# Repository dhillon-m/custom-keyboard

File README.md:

# BHOO Keyboard

A custom wireless keyboard setup with two parts. This repo has the [ZMK](https://zmk.dev) firmware, the KiCad PCB and the case CAD.

| Device      | Role             | Description                                                     |
| ----------- | ---------------- | --------------------------------------------------------------- |
| **BHOO-75** | Split central    | Custom PCB, 75% ISO (UK) with an F-row and arrow cluster. 84 keys. |
| **BHOO-20** | Split peripheral | Handwired numpad with a 128×64 SSD1306 OLED (WIP). 19 keys.      |

Both run on a **nice!nano v2** (nRF52840). The BHOO-75 pairs with the host over Bluetooth or USB. The BHOO-20 connects to the BHOO-75 as a ZMK split peripheral, so both boards share **one keymap** and appear to the computer as a single keyboard.

## Features

- **Two boards, one keymap.** Positions 0–18 are the numpad and 19–102 are the main keyboard, all defined in [`bhoo_75.keymap`](config/boards/shields/bhoo_75/bhoo_75.keymap).
- **UK layout** via [`zmk-locales`](https://github.com/joelspadin/zmk-locales) (`keys_en_gb.h`).
- **OLED battery screen (WIP)** on the BHOO-20. See [below](#oled-display-work-in-progress).
- **Bluetooth layer** for switching between 4 profiles, clearing a pairing, and entering the bootloader.
- **Custom PCB and case.** The KiCad project and STEP/STL files are in [`hardware/`](hardware). See [Hardware](#hardware).
- **CI builds** on every push through GitHub Actions. A `settings_reset` image is built too.

## OLED display (work in progress)

> **Not working yet.** Nothing shows on the screen at the moment. The code and images below are the design being worked towards, not the current behaviour.

The planned screen shows two battery bars, one per device. Each bar will fill 1 px per percent, with a hand-drawn 5×9 percentage readout next to it. At 100% the number turns into a lightning bolt. The drawing is done directly on an LVGL canvas in [`battery_screen.c`](config/boards/shields/bhoo_20/battery_screen.c).

- **Top bar:** BHOO-75.
- **Bottom bar:** BHOO-20, meant to update from `zmk_battery_state_changed`.
- The panel is mounted upside down. The overlay is set up to rotate it in hardware with `segment-remap` and `com-invdir`.
- The display should blank when the keyboard is idle (`CONFIG_ZMK_DISPLAY_BLANK_ON_IDLE`).
- Even once the screen works, the BHOO-75 bar needs more wiring: `bhoo_battery_set_central()` exists, but nothing sends the central's battery level to the peripheral yet.

## Keymap

### Layer 0: Default

**BHOO-75**

```
Esc   F1  F2  F3  F4  F5  F6  F7  F8  F9  F10 F11 F12 Del  PrtSc
`     1   2   3   4   5   6   7   8   9   0   -   =   Bksp Home
Tab   Q   W   E   R   T   Y   U   I   O   P   [   ]        End
Caps  A   S   D   F   G   H   J   K   L   ;   '   #   Ent  PgUp
Shift \   Z   X   C   V   B   N   M   ,   .   /   Shift ↑  PgDn
Ctrl  Win Alt         Space           Alt Fn  Ctrl  ←   ↓   →
```

**BHOO-20**

```
            ┌─────┬─────┐
            │  —  │  —  │
┌─────┬─────┼─────┼─────┤
│ Num │  /  │  *  │  -  │
├─────┼─────┼─────┼─────┤
│  7  │  8  │  9  │     │
├─────┼─────┼─────┤  +  │
│  4  │  5  │  6  │     │
├─────┼─────┼─────┼─────┤
│  1  │  2  │  3  │     │
├─────┴─────┼─────┤ Ent │
│     0     │  .  │     │
└───────────┴─────┴─────┘
```

The two `—` keys at the top are unassigned (`&none`).

### Layer 1: Bluetooth (hold `Fn`)

| Key    | Action                           |
| ------ | -------------------------------- |
| F1–F4  | Select Bluetooth profile 0–3     |
| F5     | Clear the current profile's bond |
| F6     | Enter bootloader (BHOO-75)       |

## Repository layout

```
.
├── build.yaml                       # Build matrix (board + shield combos)
├── .github/workflows/build.yml      # Uses ZMK's reusable build workflow (v0.2)
├── config/
│   ├── west.yml                     # Pins ZMK v0.2 + zmk-locales
│   └── boards/shields/
│       ├── bhoo_75/                 # Main keyboard: central
│       │   ├── bhoo_75.overlay      # 6×15 GPIO matrix + transform (padded to 19 cols)
│       │   ├── bhoo_75.keymap       # Keymap for both devices
│       │   └── bhoo_75.conf         # Split central
│       └── bhoo_20/                 # Numpad: peripheral
│           ├── bhoo_20.overlay      # 6×4 GPIO matrix, SSD1306 on i2c0
│           ├── bhoo_20.conf         # Display, battery, LVGL canvas
│           ├── battery_screen.c     # Custom status screen (WIP)
│           └── CMakeLists.txt
├── hardware/
│   ├── bhoo_75/pcb/                 # KiCad 8 PCB project
│   ├── bhoo_75/case/                # Top case, bottom case, plate, foot (STEP)
│   └── bhoo_20/case/                # Numpad case parts (STL)
├── docs/images/                     # Photos, renders, OLED mock-ups
└── zephyr/module.yml
```

## Building

### GitHub Actions (recommended)

1. Push to any branch, or run the workflow manually from the **Actions** tab.
2. Open the finished run and download the **firmware** artifact.
3. It contains three images:
   - `bhoo_75-nice_nano_v2-zmk.uf2`
   - `bhoo_20-nice_nano_v2-zmk.uf2`
   - `settings_reset-nice_nano_v2-zmk.uf2`

### Local build

With a [ZMK development environment](https://zmk.dev/docs/development/local-toolchain/setup) set up:

```sh
west build -s zmk/app -d build/bhoo_75 -b nice_nano_v2 -- \
  -DSHIELD=bhoo_75 -DZMK_CONFIG="$(pwd)/config"

west build -s zmk/app -d build/bhoo_20 -b nice_nano_v2 -- \
  -DSHIELD=bhoo_20 -DZMK_CONFIG="$(pwd)/config"
```

## Flashing

1. Plug the nice!nano into USB and double-tap reset. It mounts as a USB drive (`NICENANO`).
2. Copy the matching `.uf2` onto the drive. It reboots on its own when the copy finishes.
3. Do the same for the other board.

**Pairing problems?** Flash `settings_reset` to **both** boards, then reflash the normal firmware. This clears stale split and Bluetooth bonds. Afterwards, remove the keyboard from your computer's Bluetooth list and pair it again.

## Hardware

### BHOO-75: custom PCB

The BHOO-75 uses a two-layer PCB designed in KiCad 8. It's about 336 mm wide, with:

- solder-in MX switch footprints
- one SOD-123 diode per key
- a nice!nano v2 and a LiPo battery on the underside

| Layout in KiCad | Bare board |
| --- | --- |
|  |  |
| **Populated (underside)** | **Diodes up close** |
|  |  |

| File | Description |
| --- | --- |
| [`hardware/bhoo_75/pcb/`](hardware/bhoo_75/pcb) | KiCad 8 project: schematic (`PCB.kicad_sch`) and board (`PCB.kicad_pcb`) |
| [`hardware/bhoo_75/case/Top Case.step`](hardware/bhoo_75/case) | Top case |
| [`hardware/bhoo_75/case/Bottom Case.step`](hardware/bhoo_75/case) | Bottom case |
| [`hardware/bhoo_75/case/Plate.step`](hardware/bhoo_75/case) | Switch plate |
| [`hardware/bhoo_75/case/Foot.step`](hardware/bhoo_75/case) | Foot |

**Opening the PCB in KiCad:** footprints are stored inside the board file, so the PCB opens without any extra libraries. To edit the schematic symbols or see the 3D view, you also need:

- [ScottoKicad](https://github.com/joe-scotto/scottokeebs): symbols, the nice!nano and diode footprints, and 3D models. Set the `SCOTTOKEEBS_KICAD` path variable to wherever you put it.
- [ai03 MX_V2](https://github.com/ai03-2725/MX_V2): the `MX_Solderable` switch footprints.

The switch 3D models point to a file on the original author's PC, so they won't show in the 3D viewer.

### BHOO-20: handwired numpad

The BHOO-20 is handwired: switches are wired directly into a 6 × 4 matrix with diodes, no PCB. Printable case parts are in [`hardware/bhoo_20/case/`](hardware/bhoo_20/case):

- `Top Case.stl`
- `Bottom Case.stl`
- `Plate.stl`
- `Foot.stl`

### Wiring

| Board   | Matrix | Diodes  | Rows (GPIO)                         | Columns (GPIO)                                                                    |
| ------- | ------ | ------- | ----------------------------------- | --------------------------------------------------------------------------------- |
| BHOO-75 | 6 × 15 | col2row | P1.02 P1.07 P1.06 P1.04 P0.11 P1.00 | P1.01 P0.02 P0.24 P0.22 P0.20 P0.17 P0.08 P0.06 P0.09 P0.10 P1.11 P1.13 P1.15 P0.29 P0.31 |
| BHOO-20 | 6 × 4  | col2row | P0.09 P0.10 P1.11 P1.13 P1.15 P0.02 | P0.24 P1.00 P0.11 P1.04                                                           |

The BHOO-20 OLED is an SSD1306 at I²C address `0x3C` on `i2c0`, using the nice!nano default SDA/SCL pins.

The BHOO-75 matrix transform declares 19 columns. Columns 15–18 are virtual padding that reserve key positions 0–18 for the BHOO-20, so a single keymap can cover both devices.

## Roadmap

- [ ] Get the BHOO-20 OLED working
- [ ] Send the BHOO-75 battery level to the BHOO-20 display
- [ ] More layers (media, navigation)

## Acknowledgements

- [ZMK Firmware](https://zmk.dev)
- [zmk-locales](https://github.com/joelspadin/zmk-locales) by Joel Spadin
- [nice!nano](https://nicekeyboards.com/nice-nano/)
- [ScottoKicad](https://github.com/joe-scotto/scottokeebs) by Joe Scotto
- [MX_V2](https://github.com/ai03-2725/MX_V2) by ai03

## License

Everything in this repository, including the firmware, the PCB and the case CAD, is released under the [MIT License](LICENSE).

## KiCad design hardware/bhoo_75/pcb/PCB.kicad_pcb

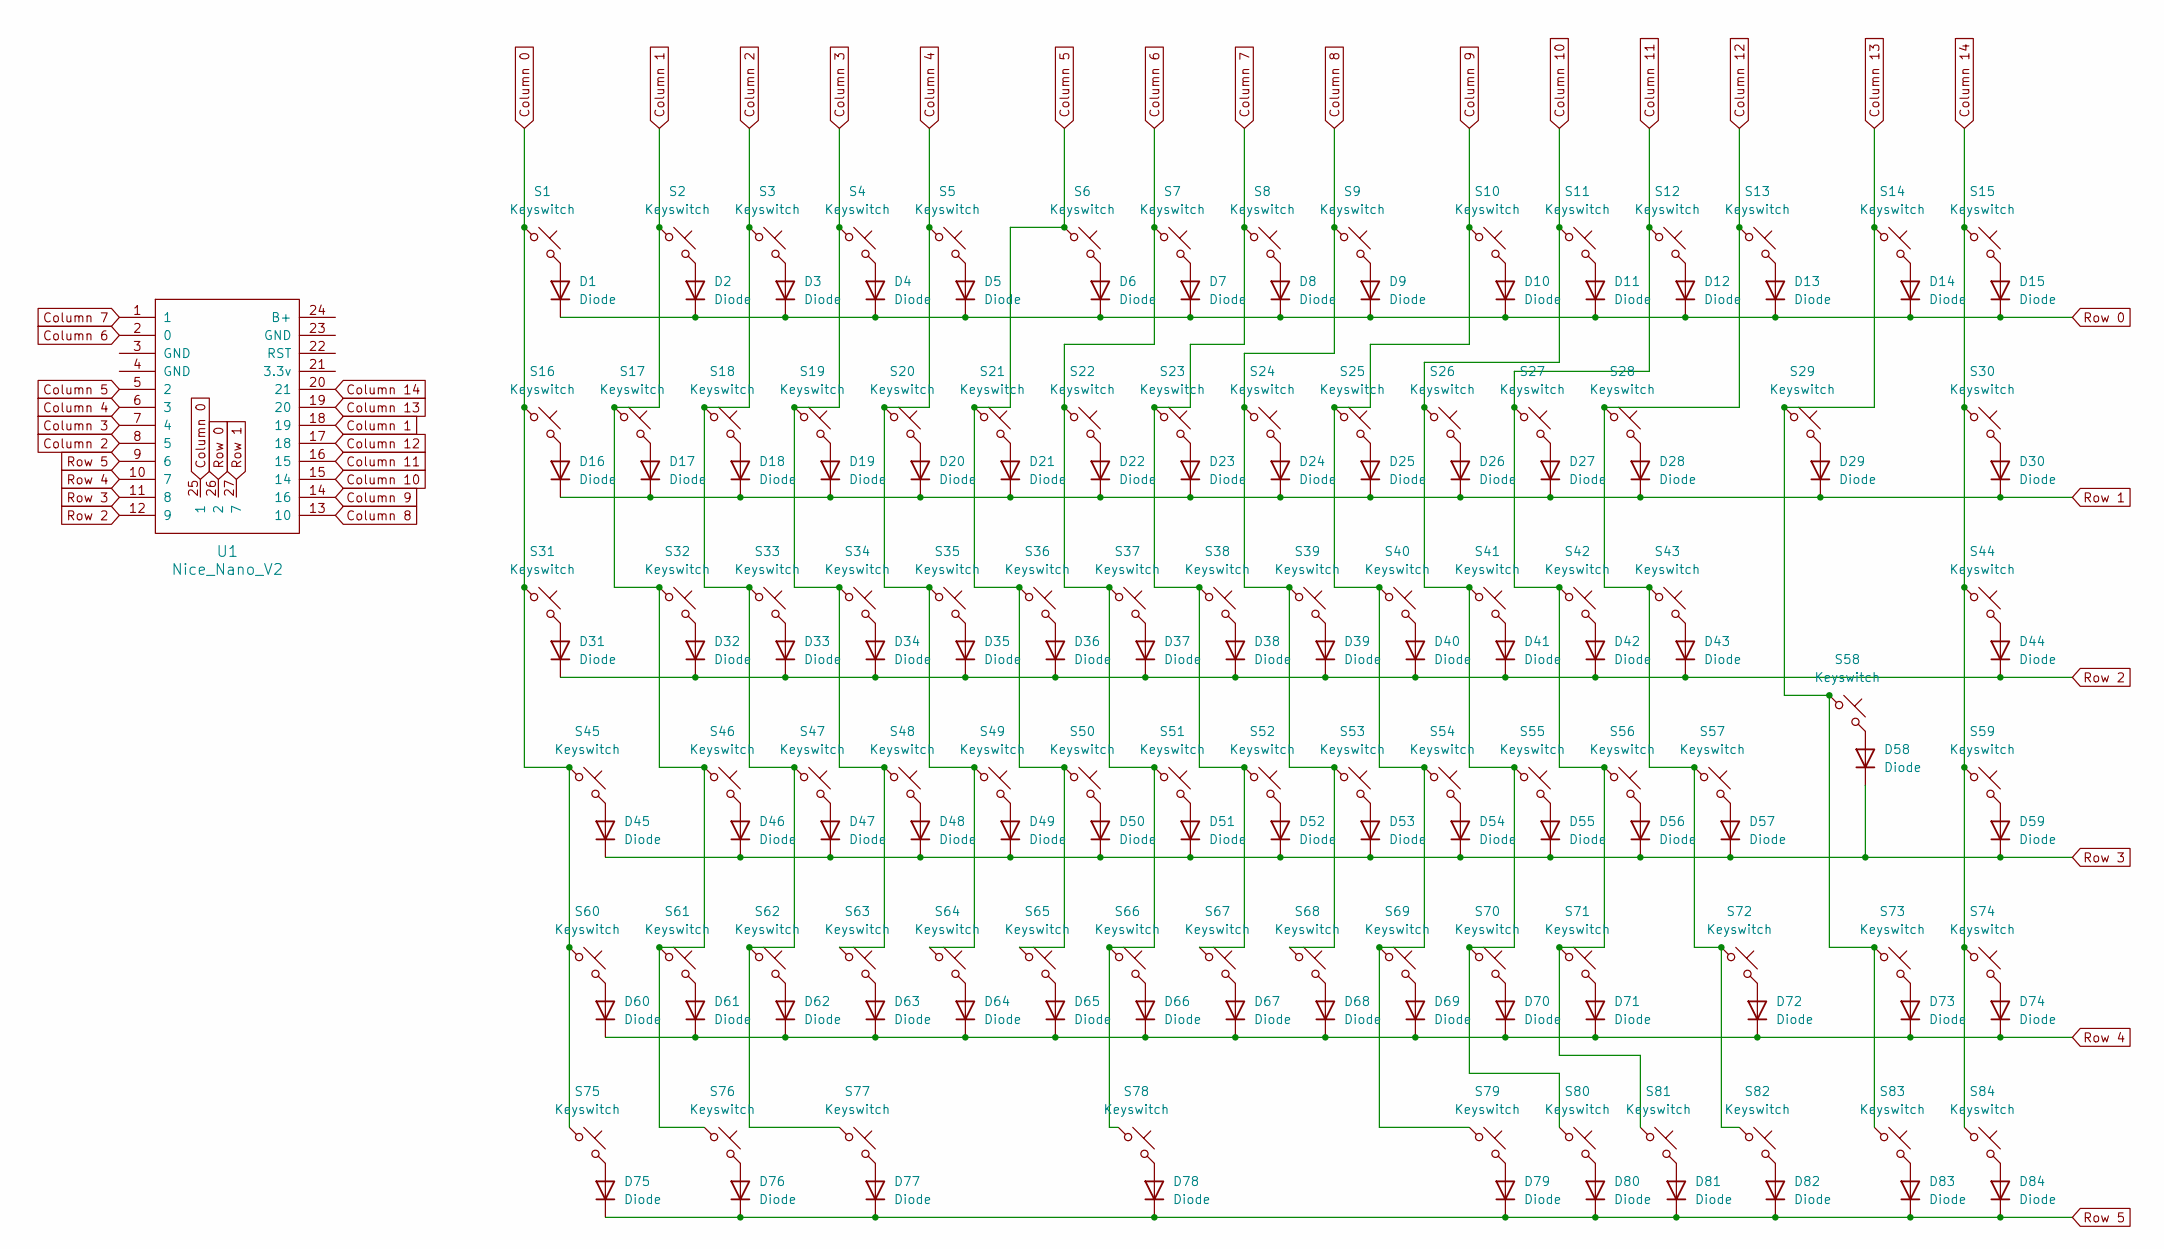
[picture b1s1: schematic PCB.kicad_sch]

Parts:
D1, D2, D3, D4, D5, D6, D7, D8, D9, D10, D11, D12, D13, D14, D15, D16, D17, D18, D19, D20, D21, D22, D23, D24, D25, D26, D27, D28, D29, D30, D31, D32, D33, D34, D35, D36, D37, D38, D39, D40, D41, D42, D43, D44, D45, D46, D47, D48, D49, D50, D51, D52, D53, D54, D55, D56, D57, D58, D59, D60, D61, D62, D63, D64, D65, D66, D67, D68, D69, D70, D71, D72, D73, D74, D75, D76, D77, D78, D79, D80, D81, D82, D83, D84: Diode; Diode_SOD-123
S1, S2, S3, S4, S5, S6, S7, S8, S9, S10, S11, S12, S13, S14, S15, S16, S17, S18, S19, S20, S21, S22, S23, S24, S25, S26, S27, S28, S30, S32, S33, S34, S35, S36, S37, S38, S39, S40, S41, S42, S43, S44, S46, S47, S48, S49, S50, S51, S52, S53, S54, S55, S56, S57, S59, S61, S62, S63, S64, S65, S66, S67, S68, S69, S70, S71, S73, S74, S79, S80, S81, S82, S83, S84: Keyswitch; MX-Solderable-1U
S29: Keyswitch; MX-Solderable-2U
S31: Keyswitch; MX-Solderable-1.5U
S45, S72: Keyswitch; MX-Solderable-1.75U
S58: Keyswitch; MX-Solderable-ISO
S60, S75, S76, S77: Keyswitch; MX-Solderable-1.25U
S78: Keyswitch; MX-Solderable-6.25U
U1: Nice_Nano_V2

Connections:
Column 0: S1.1, S16.1, S31.1, S45.1, S60.1, S75.1, U1.25 (1)
Column 1: S2.1, S17.1, S32.1, S46.1, S61.1, S76.1, U1.18 (19)
Column 2: S3.1, S18.1, S33.1, S47.1, S62.1, S77.1, U1.8 (5)
Column 3: S4.1, S19.1, S34.1, S48.1, S63.1, U1.7 (4)
Column 4: S5.1, S20.1, S35.1, S49.1, S64.1, U1.6 (3)
Column 5: S6.1, S21.1, S36.1, S50.1, S65.1, U1.5 (2)
Column 6: S7.1, S22.1, S37.1, S51.1, S66.1, S78.1, U1.2 (0)
Column 7: S8.1, S23.1, S38.1, S52.1, S67.1, U1.1
Column 8: S9.1, S24.1, S39.1, S53.1, S68.1, U1.13 (10)
Column 9: S10.1, S25.1, S40.1, S54.1, S69.1, S79.1, U1.14 (16)
Column 10: S11.1, S26.1, S41.1, S55.1, S70.1, S80.1, U1.15 (14)
Column 11: S12.1, S27.1, S42.1, S56.1, S71.1, S81.1, U1.16 (15)
Column 12: S13.1, S28.1, S43.1, S57.1, S72.1, S82.1, U1.17 (18)
Column 13: S14.1, S29.1, S58.1, S73.1, S83.1, U1.19 (20)
Column 14: S15.1, S30.1, S44.1, S59.1, S74.1, S84.1, U1.20 (21)
unnamed: D1.2 (A), S1.2
unnamed: D2.2 (A), S2.2
unnamed: D3.2 (A), S3.2
unnamed: D4.2 (A), S4.2
unnamed: D5.2 (A), S5.2
unnamed: D6.2 (A), S6.2
unnamed: D7.2 (A), S7.2
unnamed: D8.2 (A), S8.2
unnamed: D9.2 (A), S9.2
unnamed: D10.2 (A), S10.2
unnamed: D11.2 (A), S11.2
unnamed: D12.2 (A), S12.2
unnamed: D13.2 (A), S13.2
unnamed: D14.2 (A), S14.2
unnamed: D15.2 (A), S15.2
unnamed: D16.2 (A), S16.2
unnamed: D17.2 (A), S17.2
unnamed: D18.2 (A), S18.2
unnamed: D19.2 (A), S19.2
unnamed: D20.2 (A), S20.2
unnamed: D21.2 (A), S21.2
unnamed: D22.2 (A), S22.2
unnamed: D23.2 (A), S23.2
unnamed: D24.2 (A), S24.2
unnamed: D25.2 (A), S25.2
unnamed: D26.2 (A), S26.2
unnamed: D27.2 (A), S27.2
unnamed: D28.2 (A), S28.2
unnamed: D29.2 (A), S29.2
unnamed: D30.2 (A), S30.2
unnamed: D31.2 (A), S31.2
unnamed: D32.2 (A), S32.2
unnamed: D33.2 (A), S33.2
unnamed: D34.2 (A), S34.2
unnamed: D35.2 (A), S35.2
unnamed: D36.2 (A), S36.2
unnamed: D37.2 (A), S37.2
unnamed: D38.2 (A), S38.2
unnamed: D39.2 (A), S39.2
unnamed: D40.2 (A), S40.2
unnamed: D41.2 (A), S41.2
unnamed: D42.2 (A), S42.2
unnamed: D43.2 (A), S43.2
unnamed: D44.2 (A), S44.2
unnamed: D45.2 (A), S45.2
unnamed: D46.2 (A), S46.2
unnamed: D47.2 (A), S47.2
unnamed: D48.2 (A), S48.2
unnamed: D49.2 (A), S49.2
unnamed: D50.2 (A), S50.2
unnamed: D51.2 (A), S51.2
unnamed: D52.2 (A), S52.2
unnamed: D53.2 (A), S53.2
unnamed: D54.2 (A), S54.2
unnamed: D55.2 (A), S55.2
unnamed: D56.2 (A), S56.2
unnamed: D57.2 (A), S57.2
unnamed: D58.2 (A), S58.2
unnamed: D59.2 (A), S59.2
unnamed: D60.2 (A), S60.2
unnamed: D61.2 (A), S61.2
unnamed: D62.2 (A), S62.2
unnamed: D63.2 (A), S63.2
unnamed: D64.2 (A), S64.2
unnamed: D65.2 (A), S65.2
unnamed: D66.2 (A), S66.2
unnamed: D67.2 (A), S67.2
unnamed: D68.2 (A), S68.2
unnamed: D69.2 (A), S69.2
unnamed: D70.2 (A), S70.2
unnamed: D71.2 (A), S71.2
unnamed: D72.2 (A), S72.2
unnamed: D73.2 (A), S73.2
unnamed: D74.2 (A), S74.2
unnamed: D75.2 (A), S75.2
unnamed: D76.2 (A), S76.2
unnamed: D77.2 (A), S77.2
unnamed: D78.2 (A), S78.2
unnamed: D79.2 (A), S79.2
unnamed: D80.2 (A), S80.2
unnamed: D81.2 (A), S81.2
unnamed: D82.2 (A), S82.2
unnamed: D83.2 (A), S83.2
unnamed: D84.2 (A), S84.2
Row 0: D1.1 (K), D2.1 (K), D3.1 (K), D4.1 (K), D5.1 (K), D6.1 (K), D7.1 (K), D8.1 (K), D9.1 (K), D10.1 (K), D11.1 (K), D12.1 (K), D13.1 (K), D14.1 (K), D15.1 (K), U1.26 (2)
Row 1: D16.1 (K), D17.1 (K), D18.1 (K), D19.1 (K), D20.1 (K), D21.1 (K), D22.1 (K), D23.1 (K), D24.1 (K), D25.1 (K), D26.1 (K), D27.1 (K), D28.1 (K), D29.1 (K), D30.1 (K), U1.27 (7)
Row 2: D31.1 (K), D32.1 (K), D33.1 (K), D34.1 (K), D35.1 (K), D36.1 (K), D37.1 (K), D38.1 (K), D39.1 (K), D40.1 (K), D41.1 (K), D42.1 (K), D43.1 (K), D44.1 (K), U1.12 (9)
Row 3: D45.1 (K), D46.1 (K), D47.1 (K), D48.1 (K), D49.1 (K), D50.1 (K), D51.1 (K), D52.1 (K), D53.1 (K), D54.1 (K), D55.1 (K), D56.1 (K), D57.1 (K), D58.1 (K), D59.1 (K), U1.11 (8)
Row 4: D60.1 (K), D61.1 (K), D62.1 (K), D63.1 (K), D64.1 (K), D65.1 (K), D66.1 (K), D67.1 (K), D68.1 (K), D69.1 (K), D70.1 (K), D71.1 (K), D72.1 (K), D73.1 (K), D74.1 (K), U1.10 (7)
Row 5: D75.1 (K), D76.1 (K), D77.1 (K), D78.1 (K), D79.1 (K), D80.1 (K), D81.1 (K), D82.1 (K), D83.1 (K), D84.1 (K), U1.9 (6)

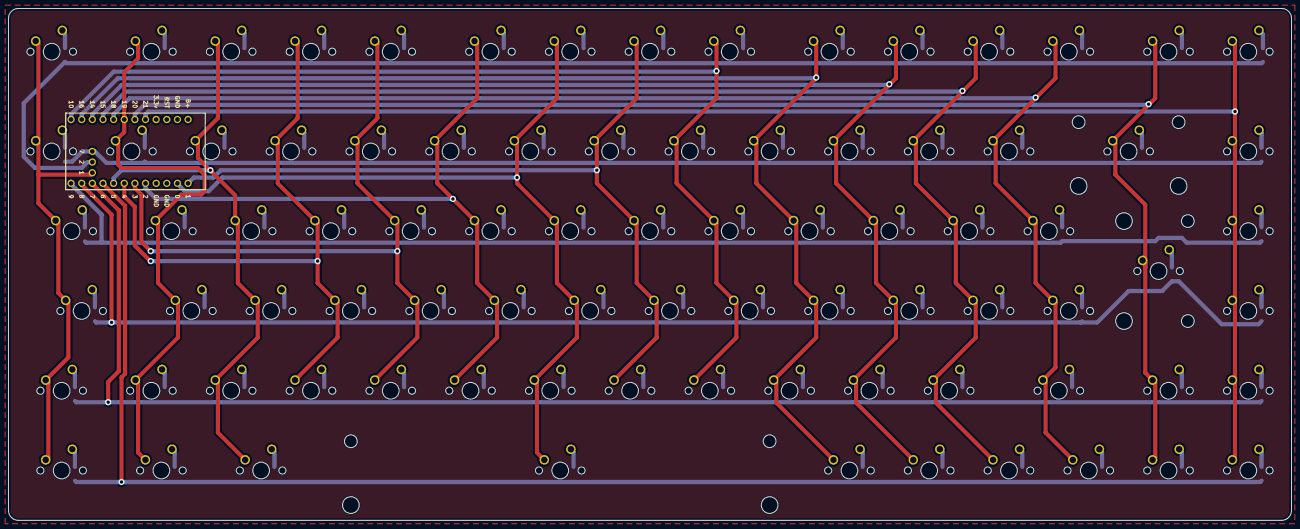
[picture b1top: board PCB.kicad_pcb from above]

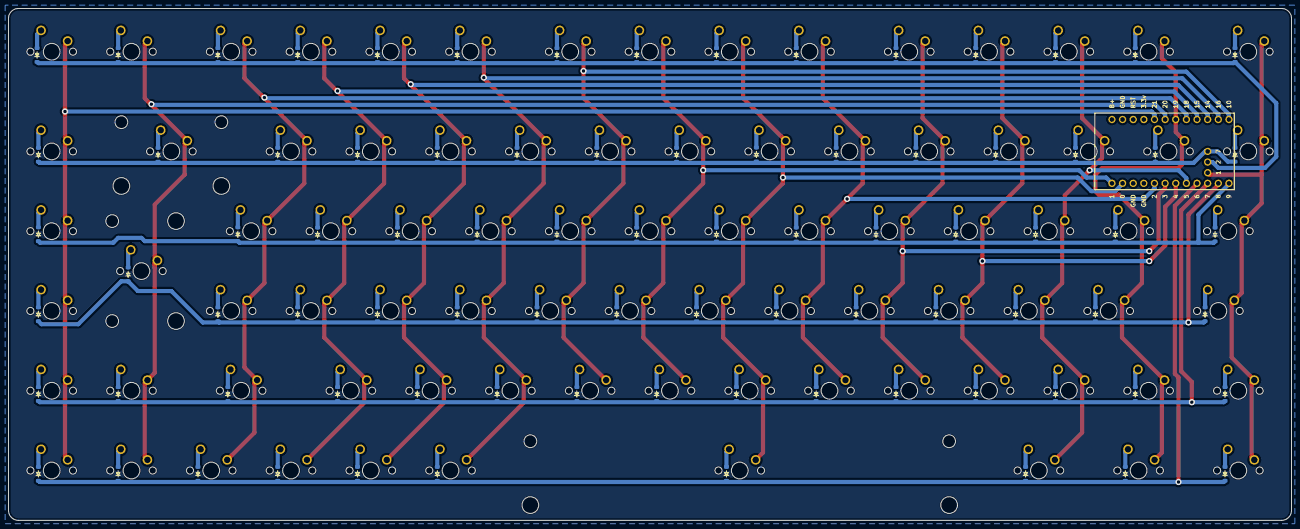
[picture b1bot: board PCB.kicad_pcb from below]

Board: 2 copper layers, 306.4 x 122.2 mm, 169 parts (85 on the bottom side), 105 nets.

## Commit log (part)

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2026-03-05 Update custom.keymap
    Changed GB_APOS to QUOT
2026-03-05 Update build.yaml
    Changed nice_nano_v2 to nice_nano. Apparently ZMK has consolidated board definitions.
2026-03-05 Update build.yaml
    revert to v2
2026-03-05 Update west.yml
    pin zmk version to v0.2
2026-03-05 Update build.yml
    pin zmk to v0.2
2026-03-05 Update build.yaml
    accidentally put V instead of v
2026-03-05 Update Kconfig.defconfig
    shortened name
2026-04-12 Added macropad shield, and marks main keyboard as split central.
2026-04-12 Drop sda and scl pin and enable &i2c
2026-04-12 Removed unecessary comments, corrected pins and added usb logging.
2026-04-12 USB logging moved to central device
2026-04-12 Removed logging - it was breaking everything
2026-04-12 simplified and treats macropad as its own device
2026-04-12 Added padding for macropad transform.
2026-04-12 gatt control
2026-04-12 Reverted gatt enforce on centrail and applied to peripheral
2026-04-12 removed padding
2026-04-12 added row padding
2026-04-12 col-offset
2026-04-13 moved padding to central
2026-04-13 Added screen functionality
2026-04-13 Added segment-offset
2026-04-13 added other oled properties
2026-05-08 Add Bluetooth configuration options for bh00_75
    Attempt to fix disconnection issues on Linux

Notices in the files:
README.md:
License: MIT
